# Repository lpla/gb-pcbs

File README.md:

# Game Boy -related custom hardware by Leopoldo Pla
Licensed under Creative Commons Attribution 4.0 International.

Files, models or projects that include PCB designs or modifications made by me. Most of them, Game Boy related.

For more hardware, check [gekkio](https://github.com/Gekkio), [HDR](https://github.com/HDR) and [insideGadgets](https://github.com/insidegadgets) profiles.

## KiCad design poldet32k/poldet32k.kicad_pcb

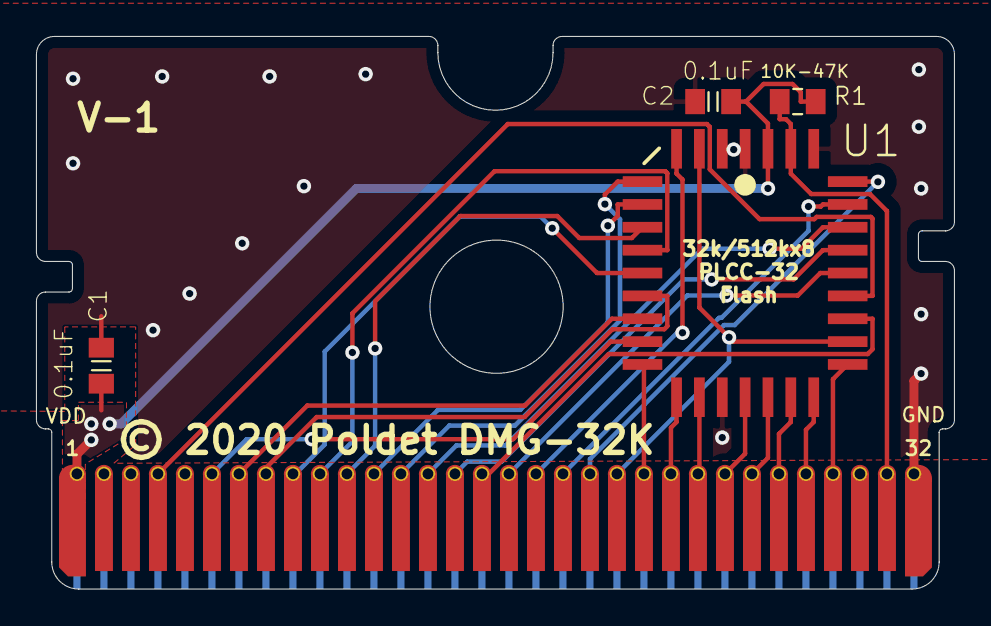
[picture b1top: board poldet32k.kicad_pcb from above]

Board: 2 copper layers, 51.0 x 30.7 mm, 6 parts (0 on the bottom side), 28 nets.

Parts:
@HOLE0: Hole
C1, C2: 0.1uF; C0805K
J1: GameBoy_GamePak_AGB-002; GameBoy_GamePak_AGB-002_P1.50mm_Edge
R1: 10K-47K; R0805_2
U1: AM29F040JNS; PLCC32R-NS

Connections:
5V: C1.1, C2.1, J1.1, R1.1, U1.32
*RD: J1.4, U1.24
A0: J1.6, U1.12
A1: J1.7, U1.11
A2: J1.8, U1.10
A3: J1.9, U1.9
A4: J1.10, U1.8
A5: J1.11, U1.7
A6: J1.12, U1.6
A7: J1.13, U1.5
A8: J1.14, U1.27
A9: J1.15, U1.26
A10: J1.16, U1.23
A11: J1.17, U1.25
A12: J1.18, U1.4
A13: J1.19, U1.28
A14: J1.20, U1.29
A15: J1.21, U1.3, U1.22
AUDIO_IN: J1.31, R1.2, U1.31
D0: J1.22, U1.13
D1: J1.23, U1.14
D2: J1.24, U1.15
D3: J1.25, U1.17
D4: J1.26, U1.18
D5: J1.27, U1.19
D6: J1.28, U1.20
D7: J1.29, U1.21
GND: C1.2, C2.2, J1.32, U1.1, U1.2, U1.16, U1.30

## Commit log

2020-09-02 Added JRodrigo mini Flash adapter
2020-09-02 Updated submodules
2023-03-23 poldet32k board
2023-03-24 Migrated some files to KiCad 7

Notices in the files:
poldet32k/poldet32k.kicad_pcb:
© 2020 Poldet DMG-32K
